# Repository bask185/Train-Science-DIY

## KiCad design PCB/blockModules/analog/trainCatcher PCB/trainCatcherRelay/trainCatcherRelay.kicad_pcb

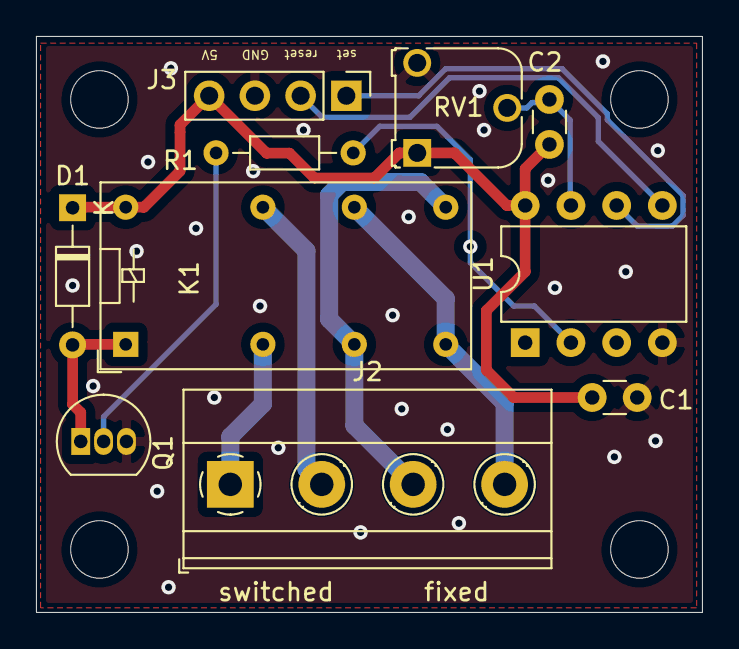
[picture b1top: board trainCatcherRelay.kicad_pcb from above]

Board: 2 copper layers, 37.0 x 32.0 mm, 10 parts (0 on the bottom side), 12 nets.

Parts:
C1, C2: C; C_Disc_D3.0mm_W1.6mm_P2.50mm
D1: D; D_DO-34_SOD68_P7.62mm_Horizontal
J2: tracks; TerminalBlock_Phoenix_MKDS-1,5-4-5.08_1x04_P5.08mm_Horizont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
J3: conn; PinHeader_1x04_P2.54mm_Vertical
K1: G5V-2; Relay_DPDT_Omron_G5V-2
Q1: BC547; TO-92_Inline
R1: R; R_Axial_DIN0204_L3.6mm_D1.6mm_P7.62mm_Horizontal
RV1: R_POT; Potentiometer_Runtron_RM-065_Vertical
U1: ATtiny45-20PU; DIP-8_W7.62mm

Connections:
+5V: C1.1, C2.1, D1.1, J3.4, K1.16, RV1.1, U1.8
/relay: R1.2, U1.2
/reset: J3.2, U1.5
/set: J3.1, U1.6
/timeDelay: C2.2, RV1.2, U1.7
GND: C1.2, J3.3, Q1.3, RV1.3, U1.4
unnamed: D1.2, K1.1, Q1.1
unnamed: J2.1, K1.4
unnamed: J2.2, K1.13
unnamed: J2.3, K1.6, K1.9
unnamed: J2.4, K1.8, K1.11
unnamed: Q1.2, R1.1

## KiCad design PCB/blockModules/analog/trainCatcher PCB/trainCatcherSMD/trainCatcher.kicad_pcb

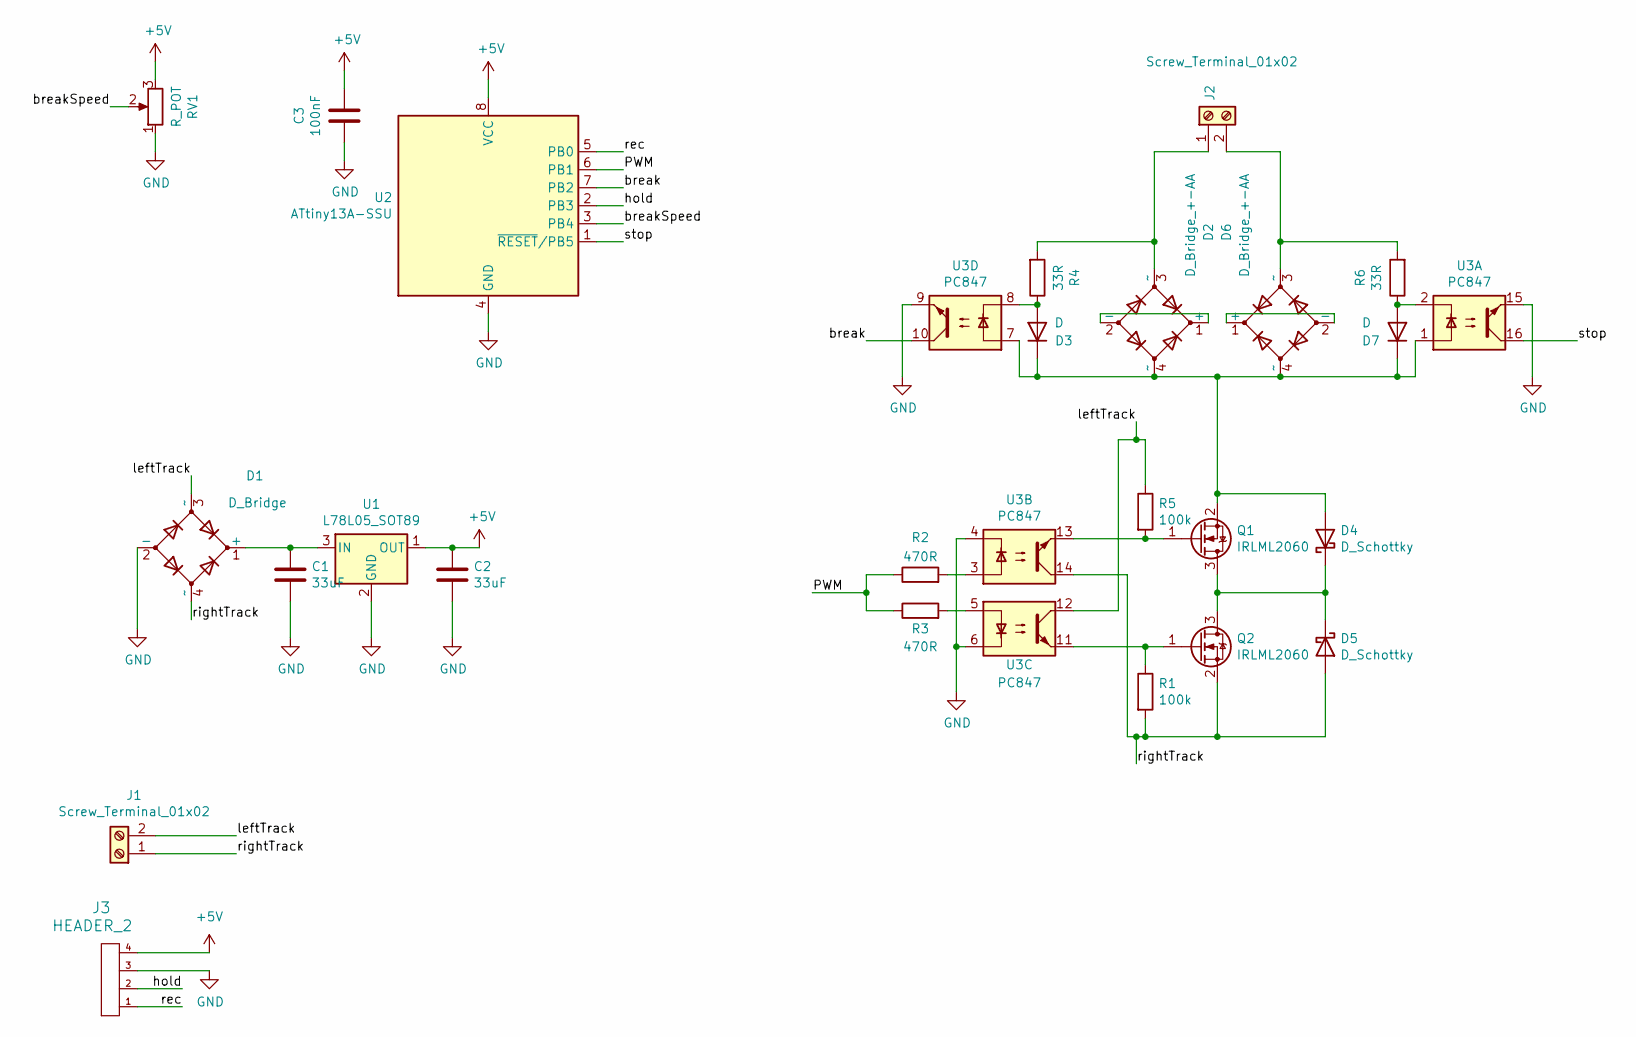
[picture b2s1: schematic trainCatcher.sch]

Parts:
C1, C2: 33uF; C_Elec_5x5.4
C3: 100nF; C_0805_2012Metric
D1: D_Bridge; TO-269AA
D2, D6: D_Bridge_+-AA; TO-269AA
D3, D7: D; D_0805_2012Metric
D4, D5: D_Schottky; D_0805_2012Metric
J1, J2: Screw_Terminal_01x02; TerminalBlock_bornier-2_P5.08mm
J3: HEADER_2; PinHeader_1x04_P2.54mm_Horizontal
Q1, Q2: IRLML2060; SOT-23
R1, R5: 100k; R_0805_2012Metric_Pad1.15x1.40mm_HandSolder
R2, R3: 470R; R_0805_2012Metric_Pad1.15x1.40mm_HandSolder
R4, R6: 33R; R_0805_2012Metric_Pad1.15x1.40mm_HandSolder
RV1: R_POT; Potentiometer_Bourns_TC33X_Vertical
U1: L78L05_SOT89; SOT-89-3
U2: ATtiny13A-SSU; SOIC-8_3.9x4.9mm_P1.27mm
U3: PC847; DIP-16_W7.62mm_SMDSocket_SmallPads

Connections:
+5V: C2.1, C3.2, J3.4, RV1.3, U1.1 (OUT), U2.8 (VCC)
/PWM: R2.1, R3.1, U2.6 (PB1)
/break: U2.7 (PB2), U3.10
/breakSpeed: RV1.2, U2.3 (PB4)
/hold: J3.2, U2.2 (PB3)
/leftTrack: D1.3 (~~), J1.2, R5.1, U3.12
/rec: J3.1, U2.5 (PB0)
/rightTrack: D1.4 (~~), D5.2 (A), J1.1, Q2.2 (S), R1.2, U3.14
/stop: U2.1 (~RESET~/PB5), U3.16
GND: C1.2, C2.2, C3.1, D1.2 (-), J3.3, RV1.1, U1.2 (GND), U2.4 (GND), U3.4, U3.6, U3.9, U3.15
unnamed: C1.1, D1.1 (+), U1.3 (IN)
unnamed: D2.1 (+), D2.2 (-)
unnamed: D2.3 (~~), J2.1, R4.2
unnamed: D2.4 (~~), D3.1 (K), D4.2 (A), D6.4 (~~), D7.1 (K), Q1.2 (S), U3.1, U3.7
unnamed: D3.2 (A), R4.1, U3.8
unnamed: D4.1 (K), D5.1 (K), Q1.3 (D), Q2.3 (D)
unnamed: D6.1 (+), D6.2 (-)
unnamed: D6.3 (~~), J2.2, R6.2
unnamed: D7.2 (A), R6.1, U3.2
unnamed: Q1.1 (G), R5.2, U3.13
unnamed: Q2.1 (G), R1.1, U3.11
unnamed: R2.2, U3.3
unnamed: R3.2, U3.5

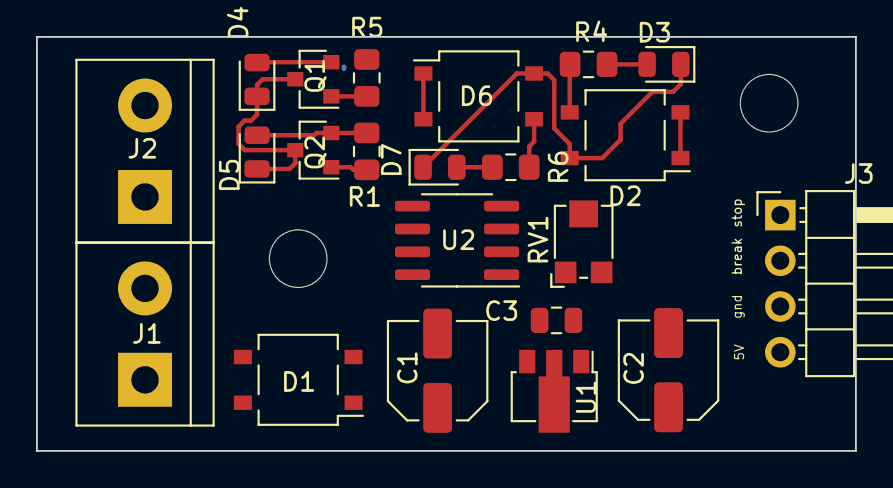
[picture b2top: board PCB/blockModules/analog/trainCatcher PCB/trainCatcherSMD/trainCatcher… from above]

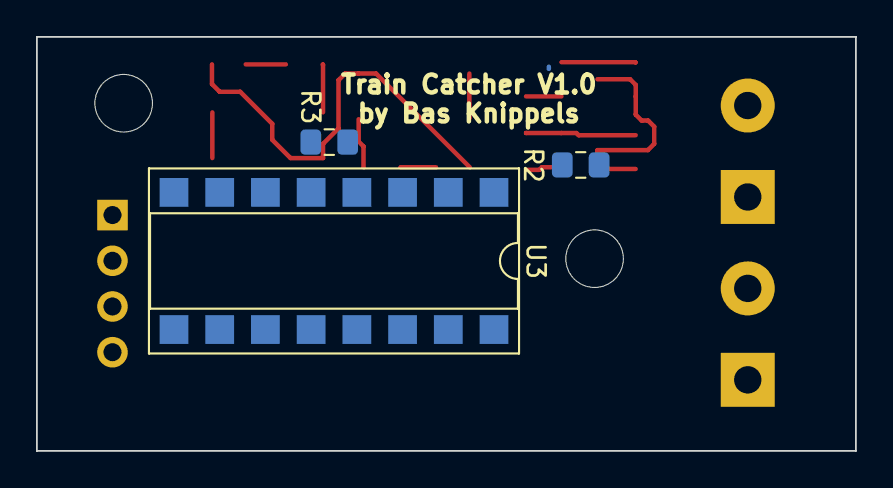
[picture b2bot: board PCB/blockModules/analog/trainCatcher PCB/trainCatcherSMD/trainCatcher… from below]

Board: 2 copper layers, 45.5 x 23.0 mm, 25 parts (3 on the bottom side), 23 nets.

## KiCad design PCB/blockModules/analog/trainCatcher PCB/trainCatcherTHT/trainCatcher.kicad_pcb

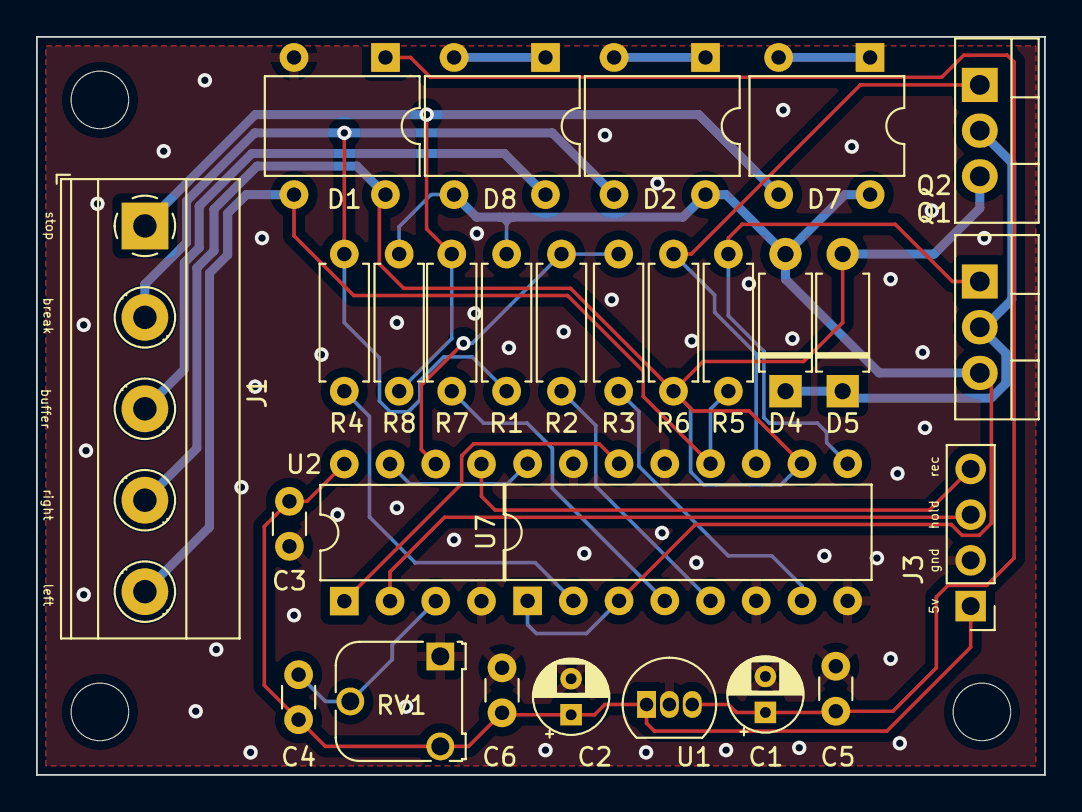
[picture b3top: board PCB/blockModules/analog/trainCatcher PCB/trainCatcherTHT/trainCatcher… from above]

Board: 2 copper layers, 56.0 x 41.0 mm, 28 parts (0 on the bottom side), 25 nets.

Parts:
C1, C2: CP; CP_Radial_D4.0mm_P2.00mm
C3, C4, C5, C6: C; C_Disc_D3.0mm_W1.6mm_P2.50mm
D1, D2, D7, D8: D; Diode_Bridge_DIP-4_W7.62mm_P5.08mm
D4, D5: D_Schottky; D_A-405_P7.62mm_Horizontal
J1: break; TerminalBlock_Phoenix_MKDS-1,5-5-5.08_1x05_P5.08mm_Horizont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
J3: Conn_01x04_Male; PinHeader_1x04_P2.54mm_Vertical
Q1, Q2: IRF540N; TO-220-3_Vertical
R1, R8: 4k7; R_Axial_DIN0207_L6.3mm_D2.5mm_P7.62mm_Horizontal
R2, R3: R; R_Axial_DIN0207_L6.3mm_D2.5mm_P7.62mm_Horizontal
R4, R7: 33R; R_Axial_DIN0207_L6.3mm_D2.5mm_P7.62mm_Horizontal
R5, R6: 100k; R_Axial_DIN0207_L6.3mm_D2.5mm_P7.62mm_Horizontal
RV1: R_POT; Potentiometer_Runtron_RM-065_Vertical
U1: MC78L05_TO92; TO-92_Inline
U2: ATtiny13-20PU; DIP-8_W7.62mm
U7: LTV-847; DIP-16_W7.62mm

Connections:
+5V: C2.1, C3.1, C4.2, C6.2, J3.1, RV1.3, U1.1 (VO), U2.8 (VCC)
/PWM: R2.2, R3.1, U2.6 (PB1)
/break: U2.7 (PB2), U7.16
/breakSection: D2.3, J1.2, R1.1, R4.2
/breakSpeed: C4.1, RV1.2, U2.3 (PB4)
/bufferSection: D8.4, J1.3
/hold: J3.3, U2.2 (PB3)
/leftMain: D1.3, J1.5, R5.1, U7.12
/rec: J3.4, U2.5 (PB0)
/rightMain: D1.4, D5.2 (A), J1.4, Q2.3 (S), R6.2, U7.10
/stop: U2.1 (~RESET/PB5), U7.14
/stopTrack: D7.3, J1.1, R7.2, R8.1
GND: C1.2, C2.2, C3.2, C5.1, C6.1, D1.2 (-), J3.2, RV1.1, U1.2 (GND), U2.4 (GND), U7.6, U7.8, U7.13, U7.15
unnamed: C1.1, C5.2, D1.1 (+), U1.3 (VI)
unnamed: D2.1 (+), D2.2 (-)
unnamed: D2.4, D4.2 (A), D7.4, D8.3, Q1.3 (S), R1.2, R8.2, U7.1, U7.3
unnamed: D4.1 (K), D5.1 (K), Q1.2 (D), Q2.2 (D)
unnamed: D7.1 (+), D7.2 (-)
unnamed: D8.1 (+), D8.2 (-)
unnamed: Q1.1 (G), R5.2, U7.9
unnamed: Q2.1 (G), R6.1, U7.11
unnamed: R2.1, U7.5
unnamed: R3.2, U7.7
unnamed: R4.1, U7.2
unnamed: R7.1, U7.4

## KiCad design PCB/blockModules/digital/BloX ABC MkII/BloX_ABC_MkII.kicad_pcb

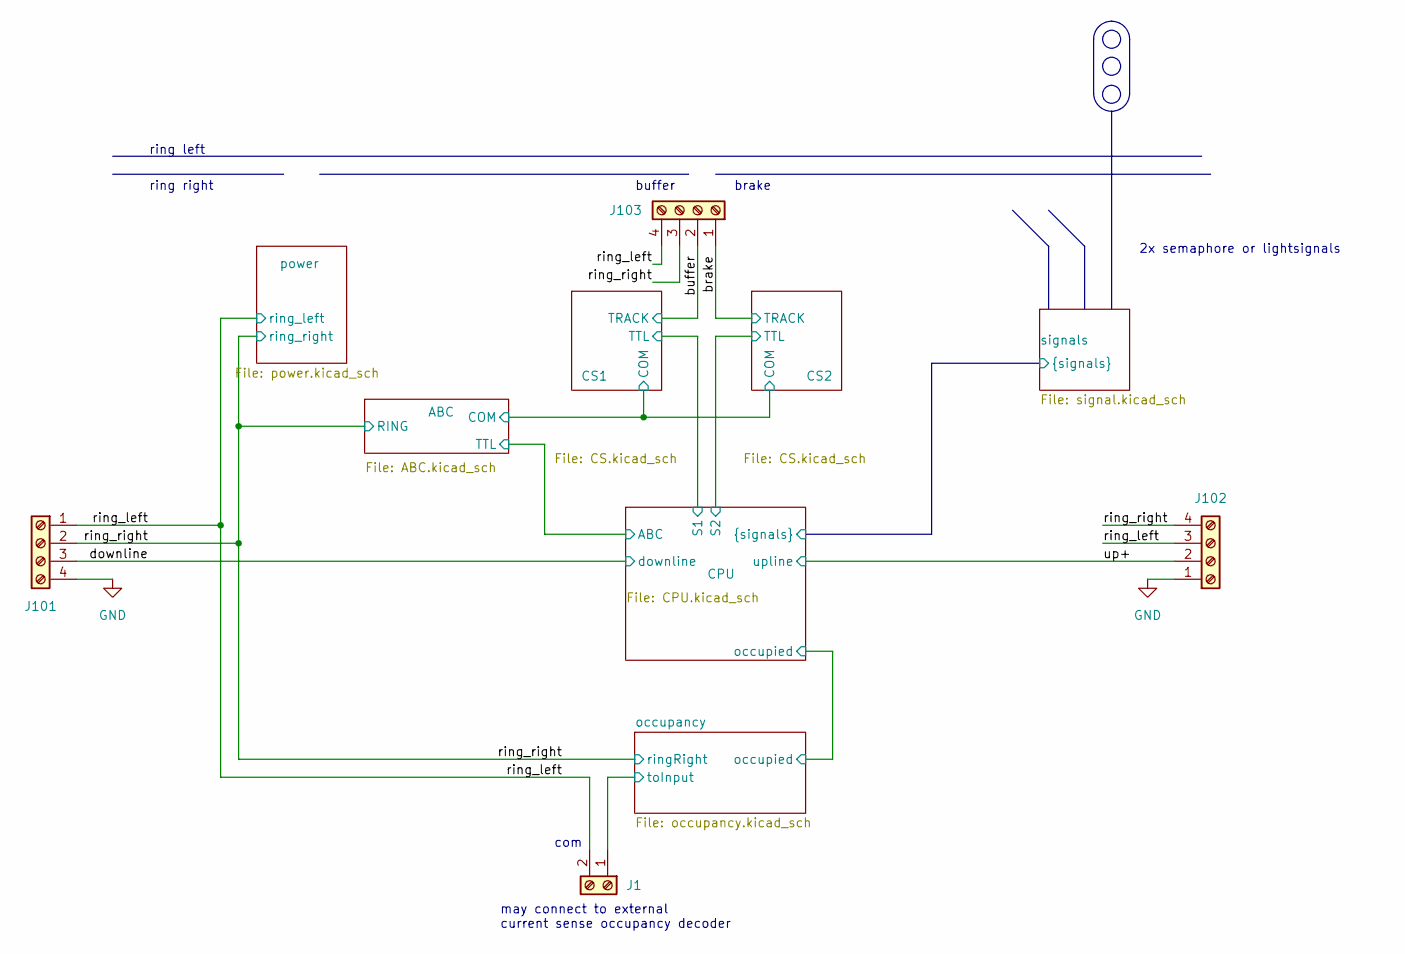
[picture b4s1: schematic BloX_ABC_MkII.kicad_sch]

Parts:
J1: Screw_Terminal_01x02; PhoenixContact_MC_1,5_2-G-3.5_1x02_P3.50mm_Horizontal
J101, J102, J103: Screw_Terminal_01x04; PhoenixContact_MC_1,5_4-G-3.5_1x04_P3.50mm_Horizontal

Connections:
/downline: J101.3; also elsewhere on the board
/occupancy/toInput: J1.1; also elsewhere on the board
/ring_left: J1.2, J101.1, J102.3, J103.4; also elsewhere on the board
/ring_right: J101.2, J102.4, J103.3; also elsewhere on the board
/up+: J102.2; also elsewhere on the board
GND: J101.4, J102.1; also elsewhere on the board

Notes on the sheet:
ring left
brake
2x semaphore or lightsignals
ring right
com
buffer
may connect to external current sense occupancy decoder

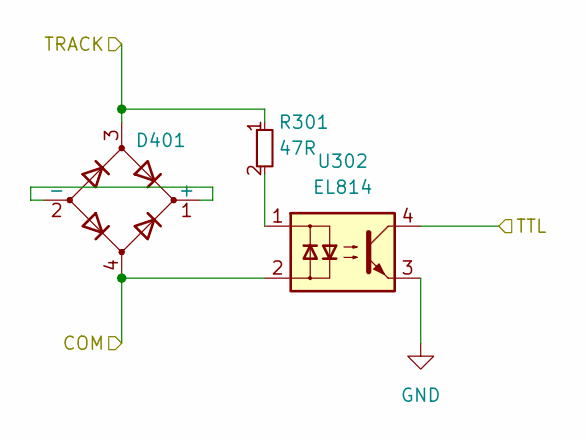
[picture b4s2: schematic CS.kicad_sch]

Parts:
D401: D_Bridge_+-AA; DB201S; JLCPCB Part# C29174
R301: 47R; R_0603_smalltext; JLCPCB Part# C23182
U302: EL814; SMDIP-4_W9.53mm; JLCPCB Part# C500388

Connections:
/ABC/COM: D401.4, U302.2; also elsewhere on the board
/CPU/S1: U302.4; also elsewhere on the board
GND: U302.3; also elsewhere on the board
unnamed: D401.1 (+), D401.2 (-)
unnamed: R301.2, U302.1

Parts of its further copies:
D301: D_Bridge_+-AA; DB201S; JLCPCB Part# C29174
R401: 47R; R_0603_smalltext; JLCPCB Part# C23182
U402: EL814; SMDIP-4_W9.53mm; JLCPCB Part# C500388

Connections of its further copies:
/ABC/COM: D301.4, U402.2; also elsewhere on the board
/CPU/S2: U402.4; also elsewhere on the board
GND: U402.3; also elsewhere on the board
unnamed: D301.1 (+), D301.2 (-)
unnamed: R401.2, U402.1

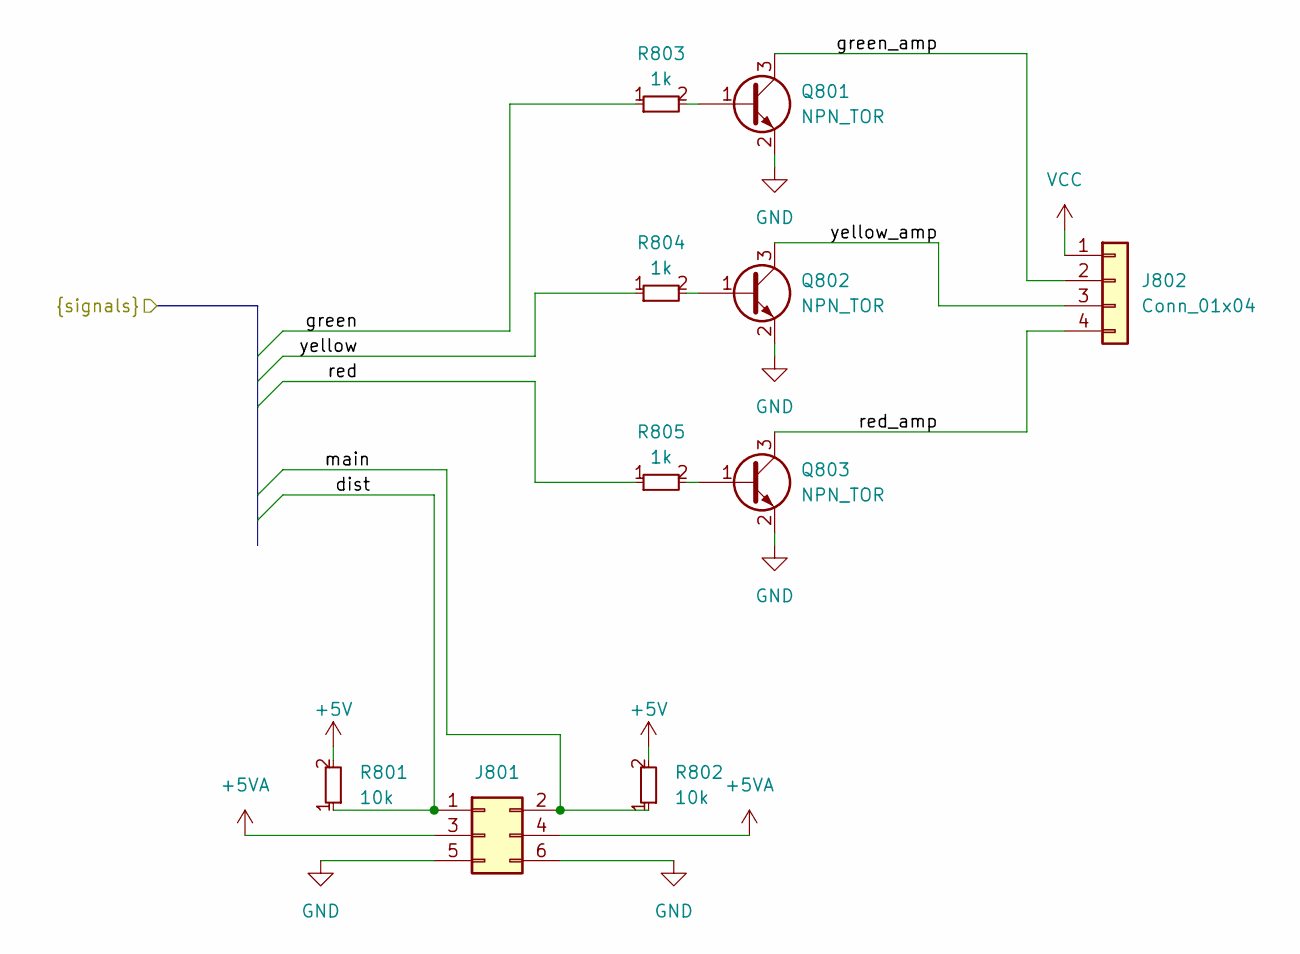
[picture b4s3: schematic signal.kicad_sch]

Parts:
J801: Conn_02x03_Odd_Even; PinHeader_2x03_P2.54mm_Vertical; JLCPCB Part# C65114
J802: Conn_01x04; PhoenixContact_MC_1,5_4-G-3.5_1x04_P3.50mm_Horizontal
Q801, Q802, Q803: NPN_TOR; SOT-23; JLCPCB Part# C2145
R801, R802: 10k; R_0603_smalltext; JLCPCB Part# C25804
R803, R804, R805: 1k; R_0603_smalltext; JLCPCB Part# C21190

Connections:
+5V: R801.2, R802.2; also elsewhere on the board
+5VA: J801.3, J801.4; also elsewhere on the board
/CPU/dist: J801.1, R801.1; also elsewhere on the board
/CPU/green: R803.1; also elsewhere on the board
/CPU/main: J801.2, R802.1; also elsewhere on the board
/CPU/red: R805.1; also elsewhere on the board
/CPU/yellow: R804.1; also elsewhere on the board
/signals/green_amp: J802.2, Q801.3 (C)
/signals/red_amp: J802.4, Q803.3 (C)
/signals/yellow_amp: J802.3, Q802.3 (C)
GND: J801.5, J801.6, Q801.2 (E), Q802.2 (E), Q803.2 (E); also elsewhere on the board
unnamed: Q801.1 (B), R803.2
unnamed: Q802.1 (B), R804.2
unnamed: Q803.1 (B), R805.2
VCC: J802.1; also elsewhere on the board

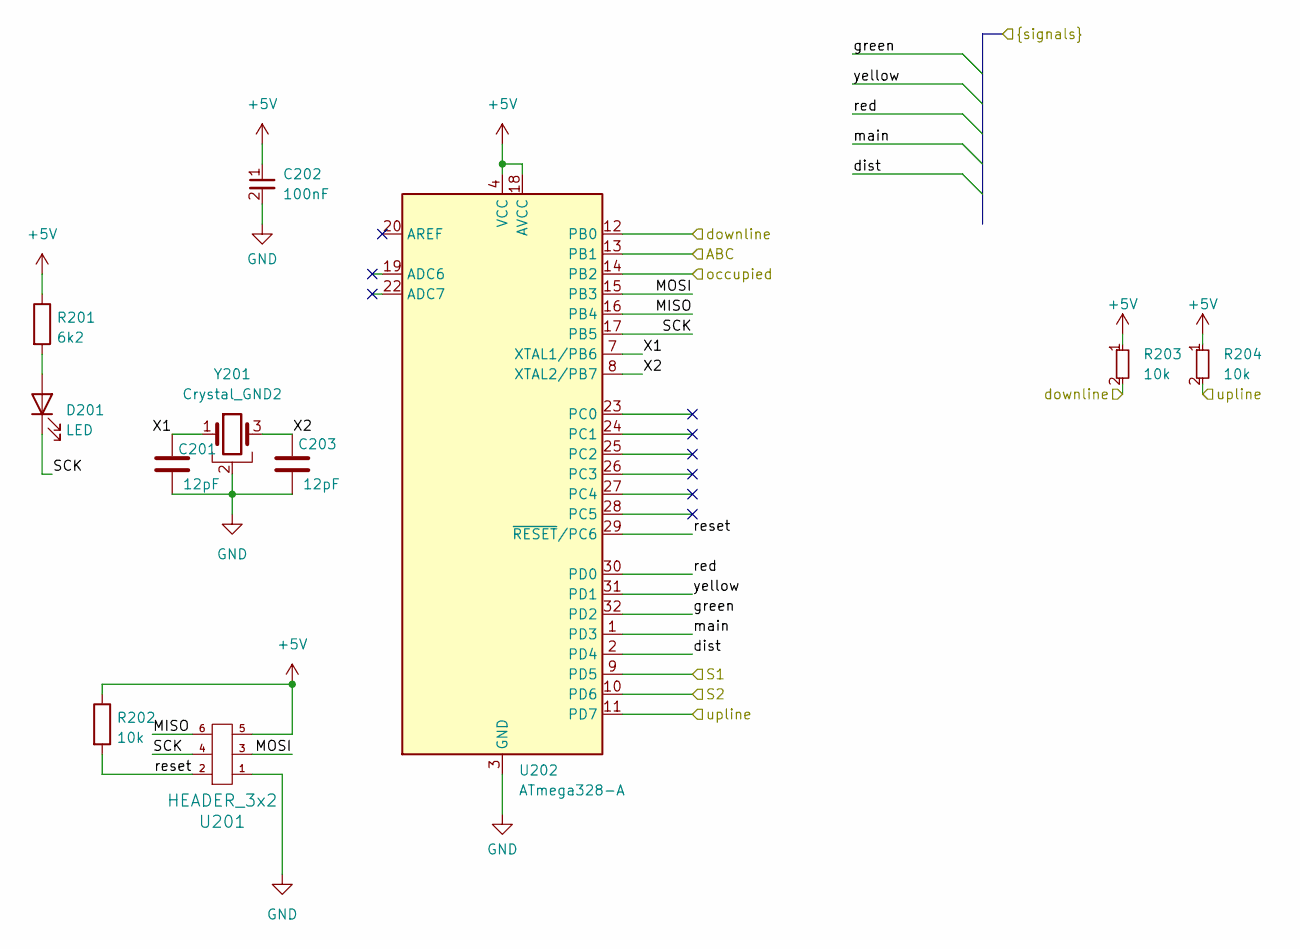
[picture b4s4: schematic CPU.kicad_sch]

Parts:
C201, C203: 12pF; C_0603_1608Metric; JLCPCB Part# C38523
C202: 100nF; C_0402_1005Metric; JLCPCB Part# C307331
D201: LED; LED_0805_2012Metric_Pad1.15x1.40mm_HandSolder; JLCPCB Part# C84256
R201: 6k2; R_0603_1608Metric_Pad0.98x0.95mm_HandSolder; JLCPCB Part# C4260
R202: 10k; R_0402_1005Metric_Pad0.72x0.64mm_HandSolder; JLCPCB Part# C25744
R203, R204: 10k; R_0603_smalltext; JLCPCB Part# C25804
U201: HEADER_3x2; PinSocket_2x03_P1.27mm_Vertical
U202: ATmega328-A; TQFP-32_7x7mm_P0.8mm; JLCPCB Part# C14877
Y201: Crystal_GND2; crystal_arduino; JLCPCB Part# C13738

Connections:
+5V: C202.1, R201.1, R202.1, R203.1, R204.1, U201.5, U202.4 (VCC), U202.6 (VCC), U202.18 (AVCC); also elsewhere on the board
/ABC/TTL: U202.13 (PB1); also elsewhere on the board
/CPU/MISO: U201.6, U202.16 (PB4)
/CPU/MOSI: U201.3, U202.15 (PB3)
/CPU/S1: U202.9 (PD5); also elsewhere on the board
/CPU/S2: U202.10 (PD6); also elsewhere on the board
/CPU/SCK: D201.1 (K), U201.4, U202.17 (PB5)
/CPU/X1: C201.2, U202.7 (XTAL1/PB6), Y201.1
/CPU/X2: C203.2, U202.8 (XTAL2/PB7), Y201.3
/CPU/dist: U202.2 (PD4); also elsewhere on the board
/CPU/green: U202.32 (PD2); also elsewhere on the board
/CPU/main: U202.1 (PD3); also elsewhere on the board
/CPU/occupied: U202.14 (PB2); also elsewhere on the board
/CPU/red: U202.30 (PD0); also elsewhere on the board
/CPU/reset: R202.2, U201.2, U202.29 (~RESET/PC6)
/CPU/yellow: U202.31 (PD1); also elsewhere on the board
/downline: R203.2, U202.12 (PB0); also elsewhere on the board
/up+: R204.2, U202.11 (PD7); also elsewhere on the board
GND: C201.1, C202.2, C203.1, U201.1, U202.3 (GND), U202.5 (GND), U202.21 (GND), Y201.2 (GND), Y201.4 (GND); also elsewhere on the board
unnamed: D201.2 (A), R201.2

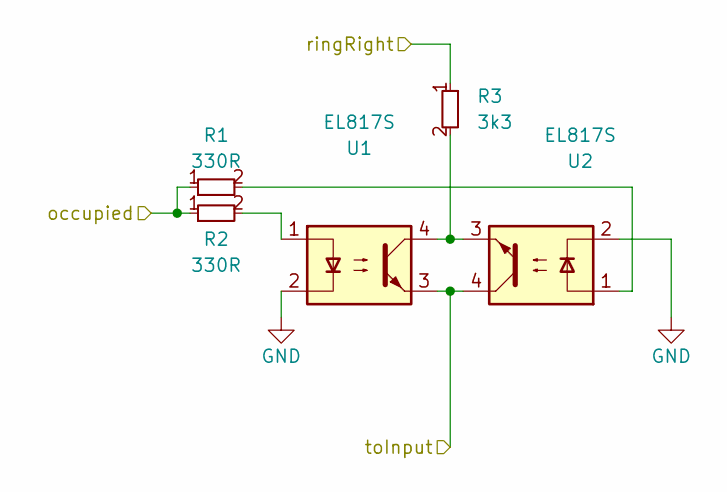
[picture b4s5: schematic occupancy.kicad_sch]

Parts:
R1, R2: 330R; R_0603_smalltext; JLCPCB Part# C23138
R3: 3k3; R_0805_handsolder-smalltext; JLCPCB Part# C26010
U1, U2: EL817S; SMDIP-4_W9.53mm; JLCPCB Part# C106900

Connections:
/CPU/occupied: R1.1, R2.1; also elsewhere on the board
/occupancy/toInput: U1.3, U2.4; also elsewhere on the board
/ring_right: R3.1; also elsewhere on the board
GND: U1.2, U2.2; also elsewhere on the board
unnamed: R1.2, U2.1
unnamed: R2.2, U1.1
unnamed: R3.2, U1.4, U2.3

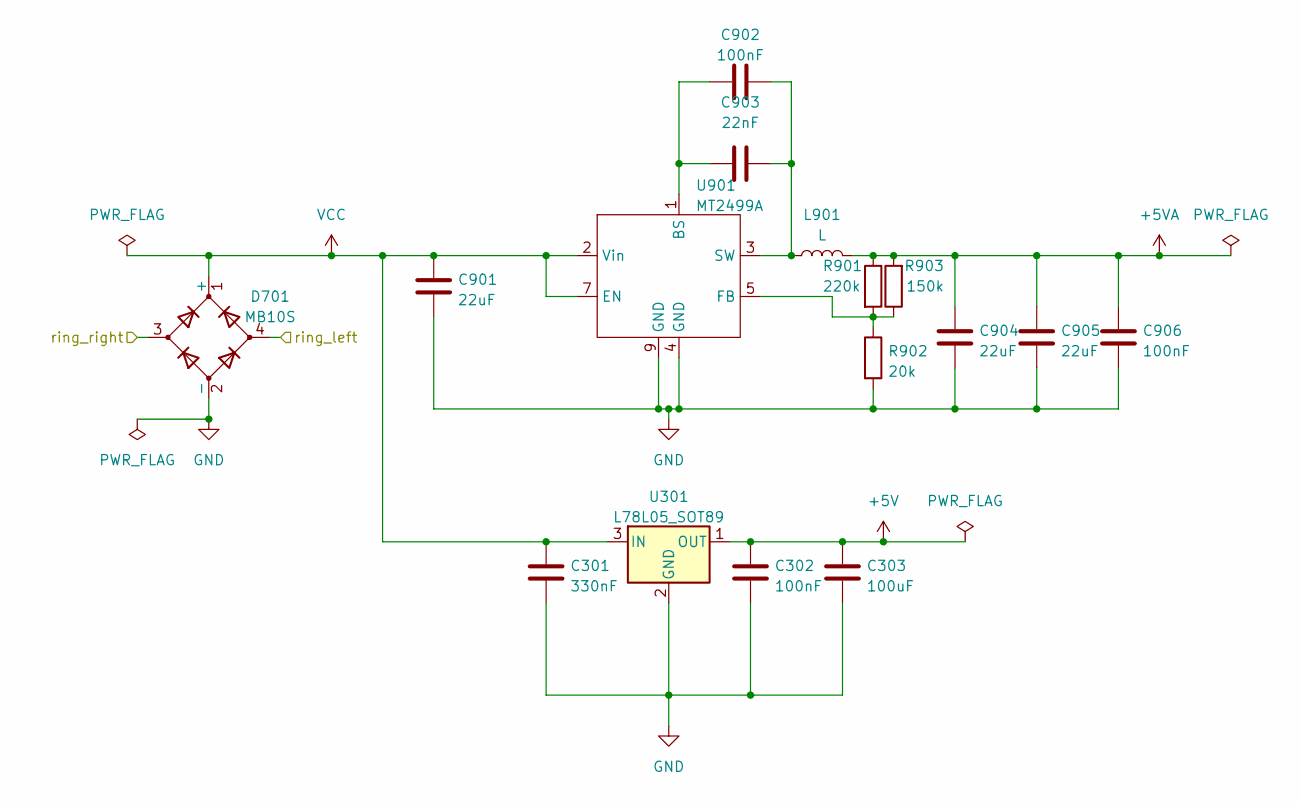
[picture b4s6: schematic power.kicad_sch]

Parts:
C301: 330nF; C_0603_1608Metric_Pad1.08x0.95mm_HandSolder; JLCPCB Part# C1615
C302: 100nF; C_0603_1608Metric_Pad1.08x0.95mm_HandSolder; JLCPCB Part# C14663
C303: 100uF; C_1206_3216Metric_Pad1.33x1.80mm_HandSolder; JLCPCB Part# C15008
C901, C904, C905: 22uF; C_0603_1608Metric; JLCPCB Part# C45783
C902, C906: 100nF; C_0402_1005Metric; JLCPCB Part# C307331
C903: 22nF; C_0402_1005Metric; JLCPCB Part# C1532
D701: MB10S; TO-269AA; JLCPCB Part# C2488
L901: L; L_Bourns-SRU8028_8.0x8.0mm; JLCPCB Part# C92945
R901: 220k; R_0603_1608Metric; JLCPCB Part# C22961
R902: 20k; R_0603_1608Metric; JLCPCB Part# C4328
R903: 150k; R_0603_1608Metric; JLCPCB Part# C22807
U301: L78L05_SOT89; SOT-89-3; JLCPCB Part# C71136
U901: MT2499A; TI_SO-PowerPAD-8; JLCPCB Part# C3007555

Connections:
+5V: C302.1, C303.1, U301.1 (OUT); also elsewhere on the board
+5VA: C904.1, C905.1, C906.1, L901.2, R901.1, R903.2; also elsewhere on the board
/ring_left: D701.4; also elsewhere on the board
/ring_right: D701.3; also elsewhere on the board
GND: C301.2, C302.2, C303.2, C901.2, C904.2, C905.2, C906.2, D701.2 (-), R902.2, U301.2 (GND), U901.4 (GND), U901.9 (GND); also elsewhere on the board
unnamed: C902.1, C903.1, U901.1 (BS)
unnamed: R901.2, R902.1, R903.1, U901.5 (FB)
unnamed: C902.2, C903.2, L901.1, U901.3 (SW)
VCC: C301.1, C901.1, D701.1 (+), U301.3 (IN), U901.2 (Vin), U901.7 (EN); also elsewhere on the board

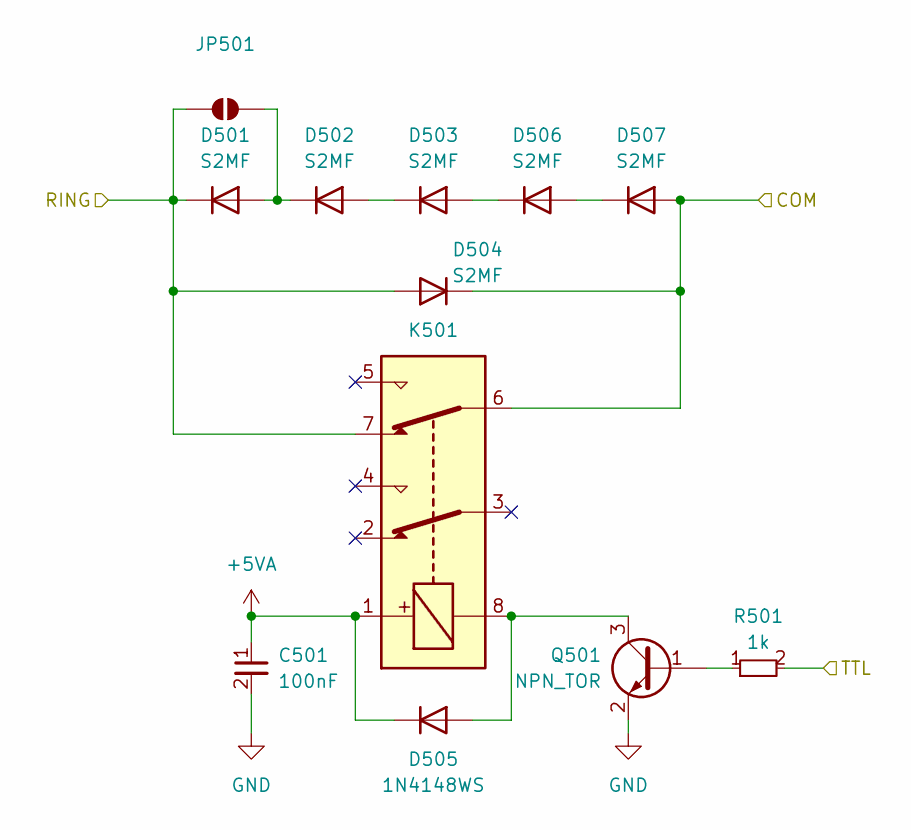
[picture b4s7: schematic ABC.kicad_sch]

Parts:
C501: 100nF; C_0402_1005Metric; JLCPCB Part# C307331
D501, D502, D503, D504, D506, D507: S2MF; S2MF_DIODE; JLCPCB Part# C5125722
D505: 1N4148WS; D_SOD-323; JLCPCB Part# C2128
JP501: SolderJumper_2_Open; SolderJumper-2_P1.3mm_Open_RoundedPad1.0x1.5mm
K501: G6K-2F-Y-TR DC5; Relay_DPDT_Omron_G6K-2F-Y; JLCPCB Part# C47190
Q501: NPN_TOR; SOT-23; JLCPCB Part# C2145
R501: 1k; R_0603_smalltext; JLCPCB Part# C21190

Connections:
+5VA: C501.1, D505.1 (K), K501.1; also elsewhere on the board
/ABC/COM: D504.1 (K), D507.2 (A), K501.6; also elsewhere on the board
/ABC/TTL: R501.2; also elsewhere on the board
/ring_right: D501.1 (K), D504.2 (A), JP501.1 (A), K501.7; also elsewhere on the board
GND: C501.2, Q501.2 (E); also elsewhere on the board
unnamed: D501.2 (A), D502.1 (K), JP501.2 (B)
unnamed: D502.2 (A), D503.1 (K)
unnamed: D503.2 (A), D506.1 (K)
unnamed: D505.2 (A), K501.8, Q501.3 (C)
unnamed: D506.2 (A), D507.1 (K)
unnamed: Q501.1 (B), R501.1

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
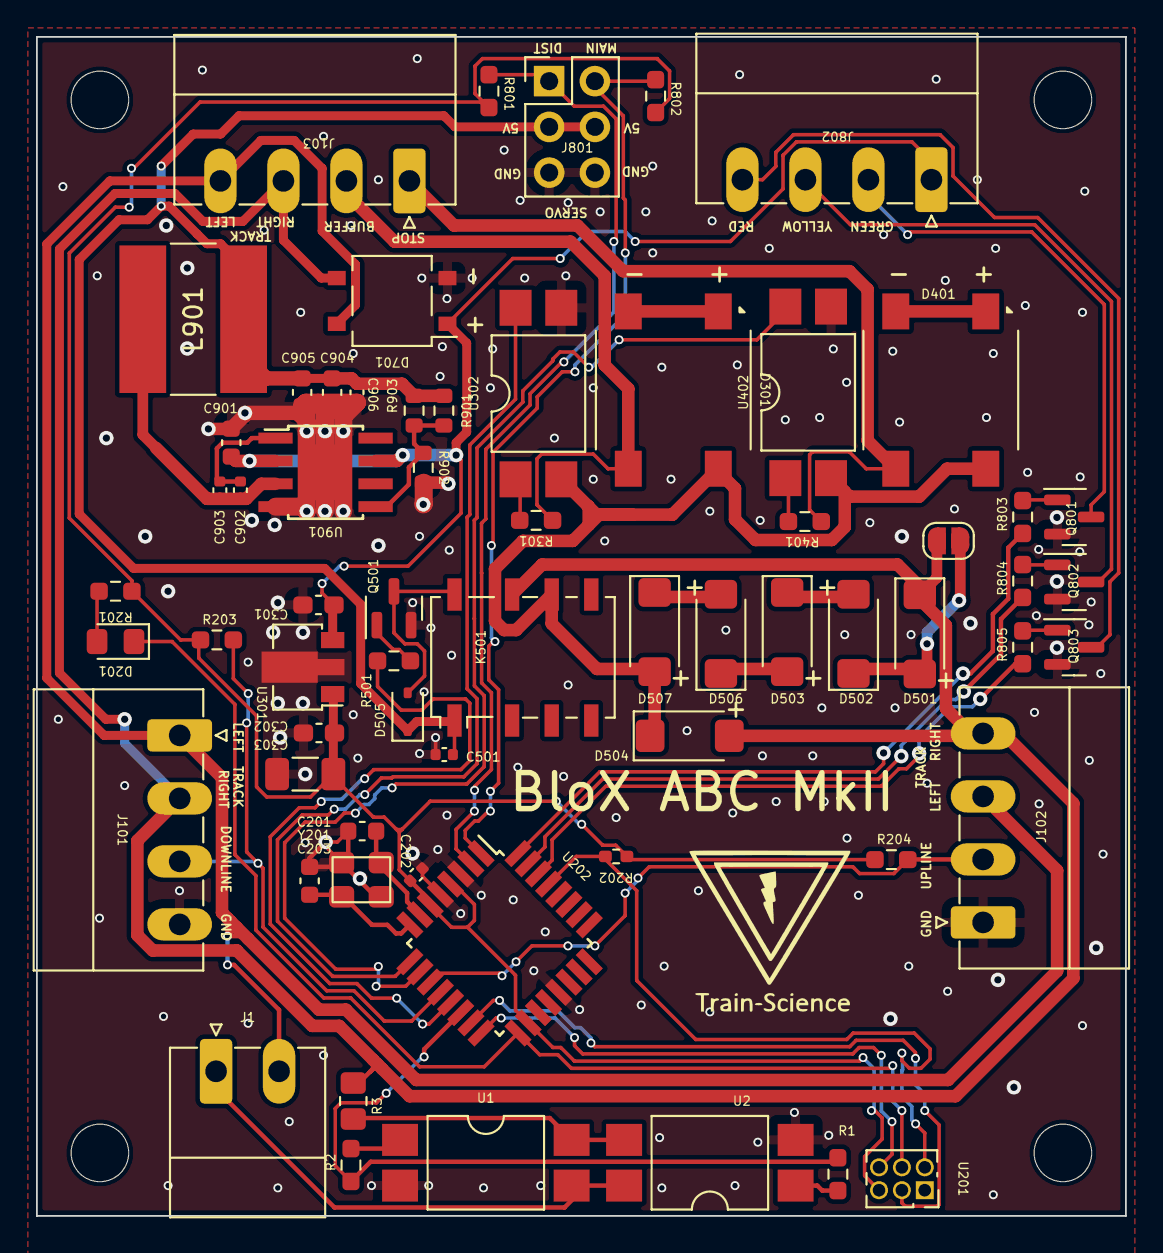
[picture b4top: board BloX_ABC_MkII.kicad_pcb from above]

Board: 2 copper layers, 60.5 x 65.5 mm, 64 parts (0 on the bottom side), 50 nets.

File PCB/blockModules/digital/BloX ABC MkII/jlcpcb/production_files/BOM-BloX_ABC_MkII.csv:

Comment,Designator,Footprint,LCSC
EL817S,"U1,U2",SMDIP-4_W9.53mm,C106900
Crystal_GND2,Y201,crystal_arduino,C13738
100nF,C302,C_0603_1608Metric_Pad1.08x0.95mm_HandSolder,C14663
ATmega328-A,U202,TQFP-32_7x7mm_P0.8mm,C14877
100uF,C303,C_1206_3216Metric_Pad1.33x1.80mm_HandSolder,C15008
22nF,C903,C_0402_1005Metric,C1532
330nF,C301,C_0603_1608Metric_Pad1.08x0.95mm_HandSolder,C1615
1k,"R501,R803,R804,R805",R_0603_smalltext,C21190
1N4148WS,D505,D_SOD-323,C2128
NPN_TOR,"Q501,Q801,Q802,Q803",SOT-23,C2145
150k,R903,R_0603_1608Metric,C22807
220k,R901,R_0603_1608Metric,C22961
330R,"R1,R2",R_0603_smalltext,C23138
47R,"R301,R401",R_0603_smalltext,C23182
MB10S,D701,TO-269AA,C2488
10k,R202,R_0402_1005Metric_Pad0.72x0.64mm_HandSolder,C25744
10k,"R203,R204,R801,R802",R_0603_smalltext,C25804
3k3,R3,R_0805_handsolder-smalltext,C26010
D_Bridge_+-AA,"D301,D401",DB201S,C29174
MT2499A,U901,TI_SO-PowerPAD-8,C3007555
100nF,"C202,C501,C902,C906",C_0402_1005Metric,C307331
12pF,"C201,C203",C_0603_1608Metric,C38523
6k2,R201,R_0603_1608Metric_Pad0.98x0.95mm_HandSolder,C4260
20k,R902,R_0603_1608Metric,C4328
22uF,"C901,C904,C905",C_0603_1608Metric,C45783
G6K-2F-Y-TR DC5,K501,Relay_DPDT_Omron_G6K-2F-Y,C47190
EL814,"U302,U402",SMDIP-4_W9.53mm,C500388
S2MF,"D501,D502,D503,D504,D506,D507",S2MF_DIODE,C5125722
Conn_02x03_Odd_Even,J801,PinHeader_2x03_P2.54mm_Vertical,C65114
L78L05_SOT89,U301,SOT-89-3,C71136
LED,D201,LED_0805_2012Metric_Pad1.15x1.40mm_HandSolder,C84256
L,L901,L_Bourns-SRN8040_8x8.15mm,C92945

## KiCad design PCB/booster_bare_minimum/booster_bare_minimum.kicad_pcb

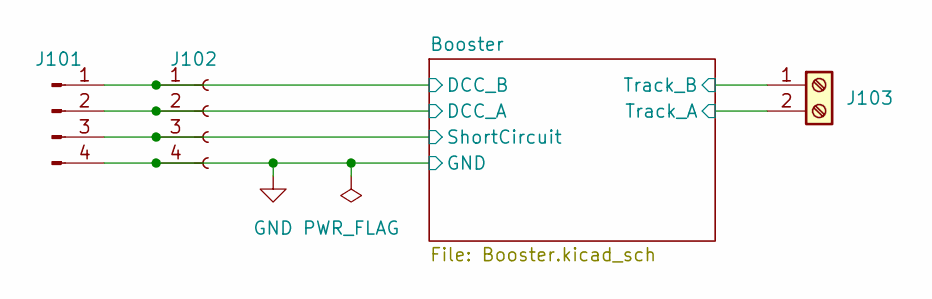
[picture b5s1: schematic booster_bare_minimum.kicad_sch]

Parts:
J101: Conn_01x04_Pin; PinHeader_1x04_P2.54mm_Horizontal; JLCPCB Part# C492412
J102: Conn_01x04_Socket; PinSocket_1x04_P2.54mm_Horizontal; JLCPCB Part# C2935994
J103: Screw_Terminal_01x02; PhoenixContact_MC_1,5_2-G-3.5_1x02_P3.50mm_Horizontal; JLCPCB Part# C2840336

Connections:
/Booster/DCC_A: J101.2, J102.2; also elsewhere on the board
/Booster/DCC_B: J101.1, J102.1; also elsewhere on the board
/Booster/ShortCircuit: J101.3, J102.3; also elsewhere on the board
/Booster/Track_A: J103.2; also elsewhere on the board
/Booster/Track_B: J103.1; also elsewhere on the board
GND: J101.4, J102.4; also elsewhere on the board

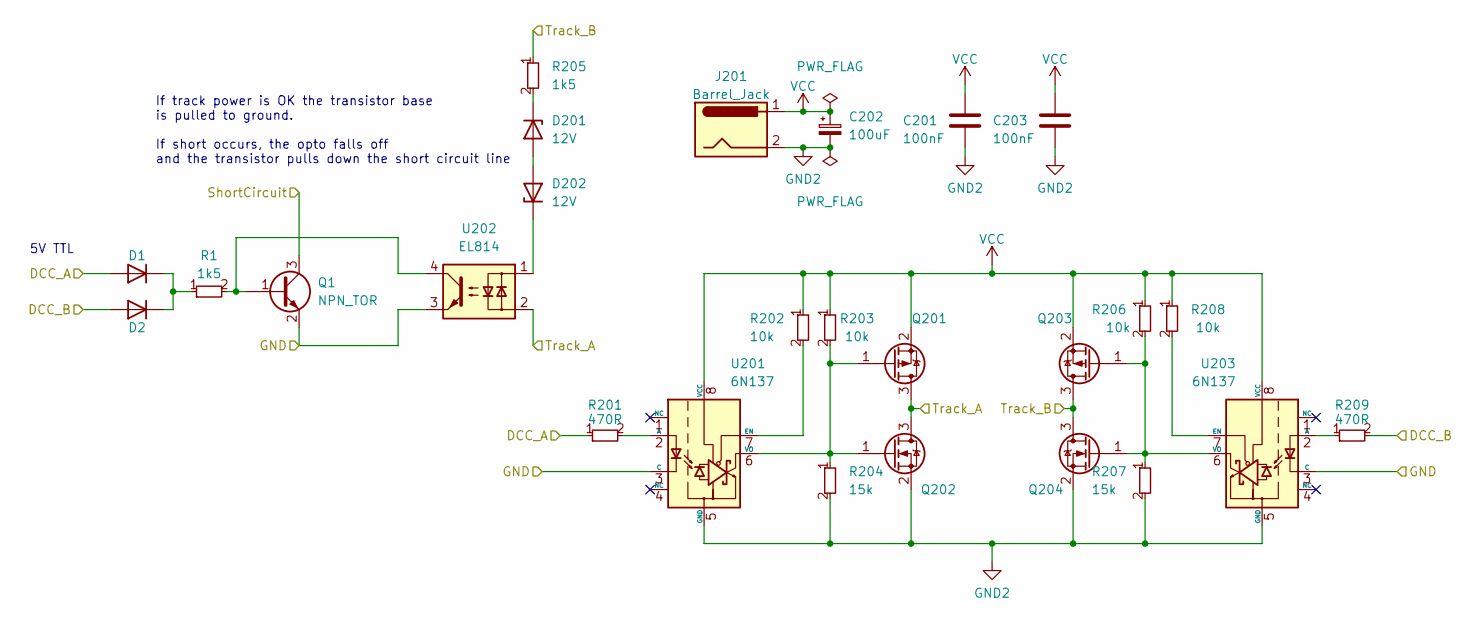
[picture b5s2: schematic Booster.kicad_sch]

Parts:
C201, C203: 100nF; C_0603_1608Metric_Pad1.08x0.95mm_HandSolder; JLCPCB Part# C14663
C202: 100uF; CP_Elec_6.3x5.9; JLCPCB Part# C494840
D1, D2: 1N4148WS; D_SOD-323; JLCPCB Part# C2128
D201, D202: 12V; D_SOD-123; JLCPCB Part# C173429
J201: Barrel_Jack; BarrelJack_GCT_DCJ200-10-A_Horizontal; JLCPCB Part# C7428747
Q1: NPN_TOR; SOT-23; JLCPCB Part# C2145
Q201, Q203: P-channel; SOT-23; JLCPCB Part# C15127
Q202, Q204: N-channel; SOT-23; JLCPCB Part# C20917
R1, R205: 1k5; R_0603_smalltext; JLCPCB Part# C22843
R201, R209: 470R; R_0603_smalltext; JLCPCB Part# C23179
R202, R203, R206, R208: 10k; R_0603_smalltext; JLCPCB Part# C25804
R204, R207: 15k; R_0603_smalltext; JLCPCB Part# C22809
U201, U203: 6N137; SOP-8_6.605x9.655mm_P2.54mm; JLCPCB Part# C110020
U202: EL814; SMDIP-4_W9.53mm; JLCPCB Part# C500388

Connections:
/Booster/DCC_A: D1.2 (A), R201.1; also elsewhere on the board
/Booster/DCC_B: D2.2 (A), R209.2; also elsewhere on the board
/Booster/ShortCircuit: Q1.3 (C); also elsewhere on the board
/Booster/Track_A: Q201.3 (D), Q202.3 (D), U202.2; also elsewhere on the board
/Booster/Track_B: Q203.3 (D), Q204.3 (D), R205.1; also elsewhere on the board
GND: Q1.2 (E), U201.3 (C), U202.3, U203.3 (C); also elsewhere on the board
GND2: C201.1, C202.2, C203.1, J201.2, Q202.2 (S), Q204.2 (S), R204.2, R207.2, U201.5 (GND), U203.5 (GND)
unnamed: D1.1 (K), D2.1 (K), R1.1
unnamed: D201.2 (A), D202.2 (A)
unnamed: D201.1 (K), R205.2
unnamed: D202.1 (K), U202.1
unnamed: Q1.1 (B), R1.2, U202.4
unnamed: Q201.1 (G), Q202.1 (G), R203.2, R204.1, U201.6 (VO)
unnamed: Q203.1 (G), Q204.1 (G), R206.2, R207.1, U203.6 (VO)
unnamed: R201.2, U201.2 (A)
unnamed: R202.2, U201.7 (EN)
unnamed: R209.1, U203.2 (A)
unnamed: R208.2, U203.7 (EN)
VCC: C201.2, C202.1, C203.2, J201.1, Q201.2 (S), Q203.2 (S), R202.1, R203.1, R206.1, R208.1, U201.8 (VCC), U203.8 (VCC)

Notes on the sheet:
If track power is OK the transistor base is pulled to ground. If short occurs, the opto falls off and the transistor pulls down the short circuit line
5V TTL
